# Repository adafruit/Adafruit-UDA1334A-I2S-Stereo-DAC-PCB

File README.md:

## Adafruit UDA1334A I2S Stereo DAC PCB

<a href="http://www.adafruit.com/products/3678"><br/>
Click here to purchase one from the Adafruit shop</a>

PCB files for the Adafruit UDA1334A I2S Stereo DAC Breakout. Format is EagleCAD schematic and board layout

For more details, check out the product page at
* https://www.adafruit.com/products/3678

### Description

This fully-featured UDA1334A I2S Stereo DAC breakout is a perfect match for any I2S-output audio interface. It's affordable but sounds great! The NXP UDA1334A is a jack-of-all-I2S-trades: you can use 3.3V - 5V logic levels (a rarity), and can process multiple different formats by setting two pins to high or low. The DAC will process data immediately, and give you a clear, analog, stereo line level output. It's even cool with MCLK-less I2S interfaces such as the Raspberry Pi (which it's ideal for) - a built in PLL will generate the proper clock from the bitclock signal.

For inputs, you can use classic I2S (the default) or 16-bit, 20-bit or 24-bit left justified data. You can set it up to take an input system/master clock but we default-set it to just generate it for you, so you only need to connect Data In, Word Select (Left/Right Clock) and Bit Clock lines. If you want, there's a mute pin and a de-emphasis filter you can turn on.

We put in plenty of ferrite beads, a low-dropout regulator, and the recommended band-pass filter so you get a very nice clean output. With a sine-wave generator we swept through 20-20KHz and saw no attenuation or distortion. Plug into either the 3.5mm stereo headphone jack or the breadboard-friendly pads. We think you'll be pleased with this DAC!

Each order comes with one I2S Stereo DAC breakout and some header you can solder on. 

### License

Adafruit invests time and resources providing this open source design, please support Adafruit and open-source hardware by purchasing products from [Adafruit](https://www.adafruit.com)!

Designed by Limor Fried/Ladyada for Adafruit Industries.

Creative Commons Attribution/Share-Alike, all text above must be included in any redistribution. See license.txt for additional details.

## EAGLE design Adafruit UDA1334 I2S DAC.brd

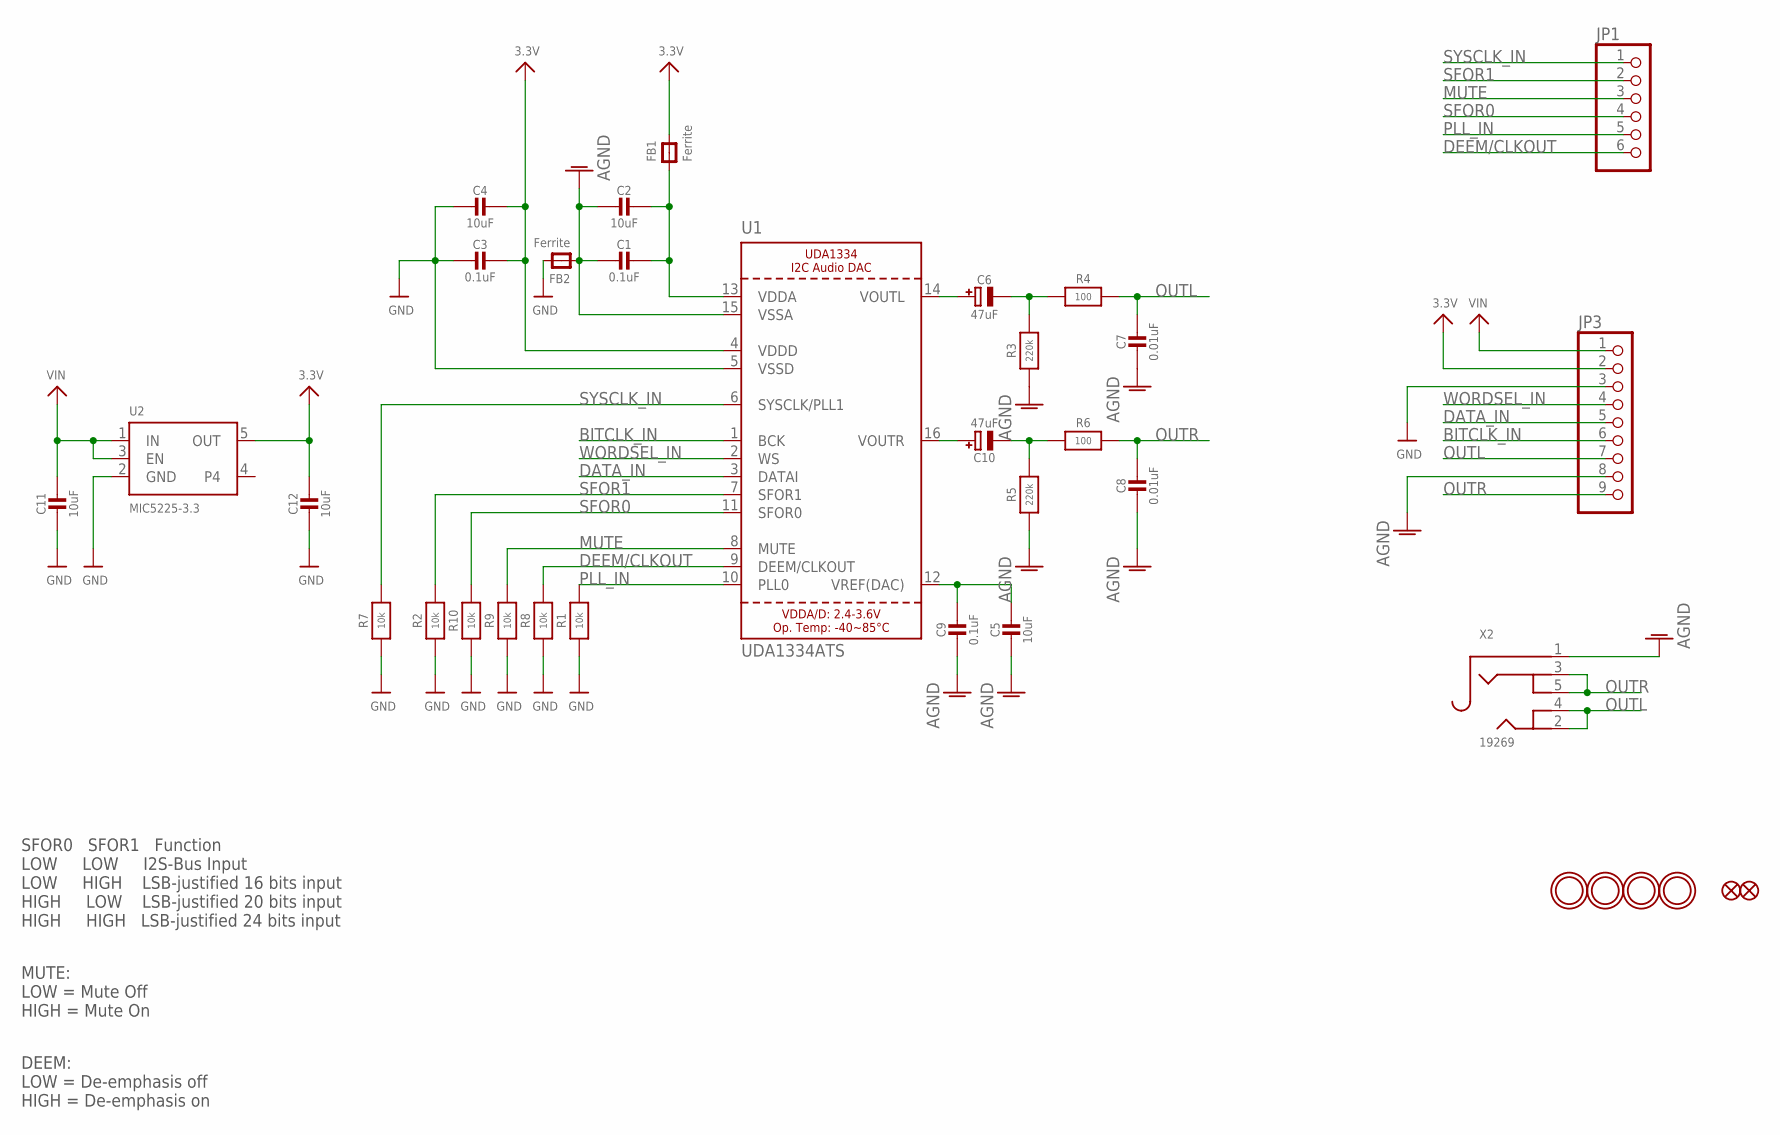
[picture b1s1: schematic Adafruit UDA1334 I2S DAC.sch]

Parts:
C1, C3, C9: 0.1uF; 0805-NO
C2, C4, C5, C11, C12: 10uF; 0805-NO
C6, C10: 47uF; PANASONIC_C
C7, C8: 0.01uF; 0805-NO
FB1, FB2: Ferrite; 0805
FID1, FID2: FIDUCIAL_1MM
JP1: HEADER-1X670MIL; 1X06_ROUND_70
JP3: HEADER-1X970MIL; 1X09_ROUND_70
R1, R2, R7, R8, R9, R10: 10k; 0603-NO
R3, R5: 220k; 0805-NO
R4, R6: 100; 0805-NO
U1: UDA1334ATS; SSOP16_4.4MM
U2: MIC5225-3.3; SOT23-5
U$11, U$12, U$13, U$14: MOUNTINGHOLE2.5; MOUNTINGHOLE_2.5_PLATED
X2: 19269; 4UCONN_19269

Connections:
3.3V: C3.1, C4.1, C12.1, FB1.2, JP3.2, U1.4 (VDDD), U2.5 (OUT)
AGND: C1.2, C2.2, C5.2, C7.2, C8.2, C9.2, FB2.1, JP3.8, R3.1, R5.1, U1.15 (VSSA), X2.1
BITCLK_IN: JP3.6, U1.1 (BCK)
DATA_IN: JP3.5, U1.3 (DATAI)
DEEM/CLKOUT: JP1.6, R8.2, U1.9 (DEEM/CLKOUT)
GND: C3.2, C4.2, C11.2, C12.2, FB2.2, JP3.3, R1.1, R2.1, R7.1, R8.1, R9.1, R10.1, U1.5 (VSSD), U2.2 (GND)
MUTE: JP1.3, R9.2, U1.8 (MUTE)
unnamed: C5.1, C9.1, U1.12 (VREF(DAC))
unnamed: C1.1, C2.1, FB1.1, U1.13 (VDDA)
unnamed: C10.+, U1.16 (VOUTR)
unnamed: C6.+, U1.14 (VOUTL)
unnamed: C6.-, R3.2, R4.1
unnamed: C10.-, R5.2, R6.1
OUTL: C7.1, JP3.7, R4.2, X2.2, X2.4
OUTR: C8.1, JP3.9, R6.2, X2.3, X2.5
PLL_IN: JP1.5, R1.2, U1.10 (PLL0)
SFOR0: JP1.4, R10.2, U1.11 (SFOR0)
SFOR1: JP1.2, R2.2, U1.7 (SFOR1)
SYSCLK_IN: JP1.1, R7.2, U1.6 (SYSCLK/PLL1)
VIN: C11.1, JP3.1, U2.1 (IN), U2.3 (EN)
WORDSEL_IN: JP3.4, U1.2 (WS)

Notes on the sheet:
MUTE: LOW = Mute Off HIGH = Mute On
DEEM: LOW = De-emphasis off HIGH = De-emphasis on
SFOR0 SFOR1 Function LOW LOW I2S-Bus Input LOW HIGH LSB-justified 16 bits input HIGH LOW LSB-justified 20 bits input HIGH HIGH LSB-justified 24 bits input

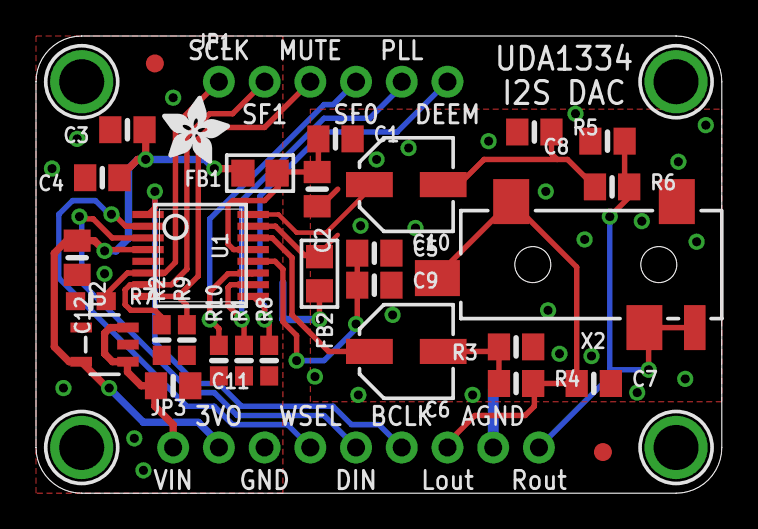
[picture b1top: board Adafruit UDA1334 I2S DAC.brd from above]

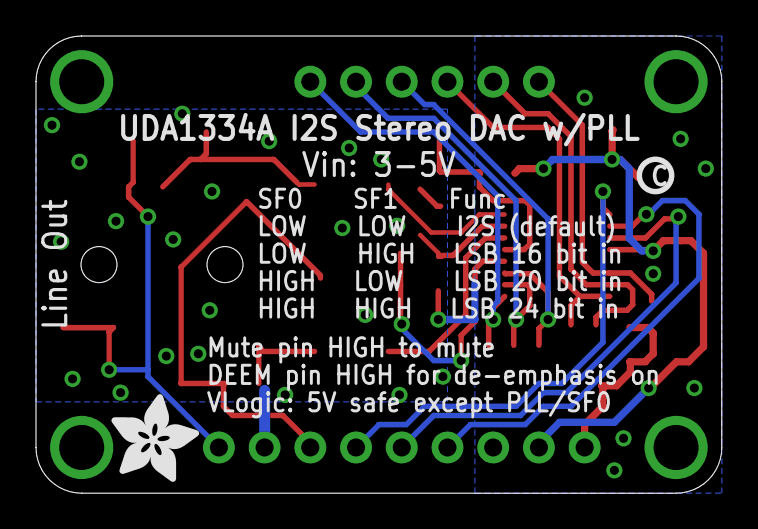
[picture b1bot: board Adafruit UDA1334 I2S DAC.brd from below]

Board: 2 copper layers, 38.1 x 25.4 mm, 38 parts (2 on the bottom side), 21 nets.

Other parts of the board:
U$5: PCBFEAT-REV-040
U$6: ADAFRUIT_5MM
U$29: ADAFRUIT_3.5MM

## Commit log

2017-11-22 init

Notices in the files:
parts and their libraries:
microbuilder: This work is placed in the public domain, and may be freely used for commercial and non-commercial work with the following conditions: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
